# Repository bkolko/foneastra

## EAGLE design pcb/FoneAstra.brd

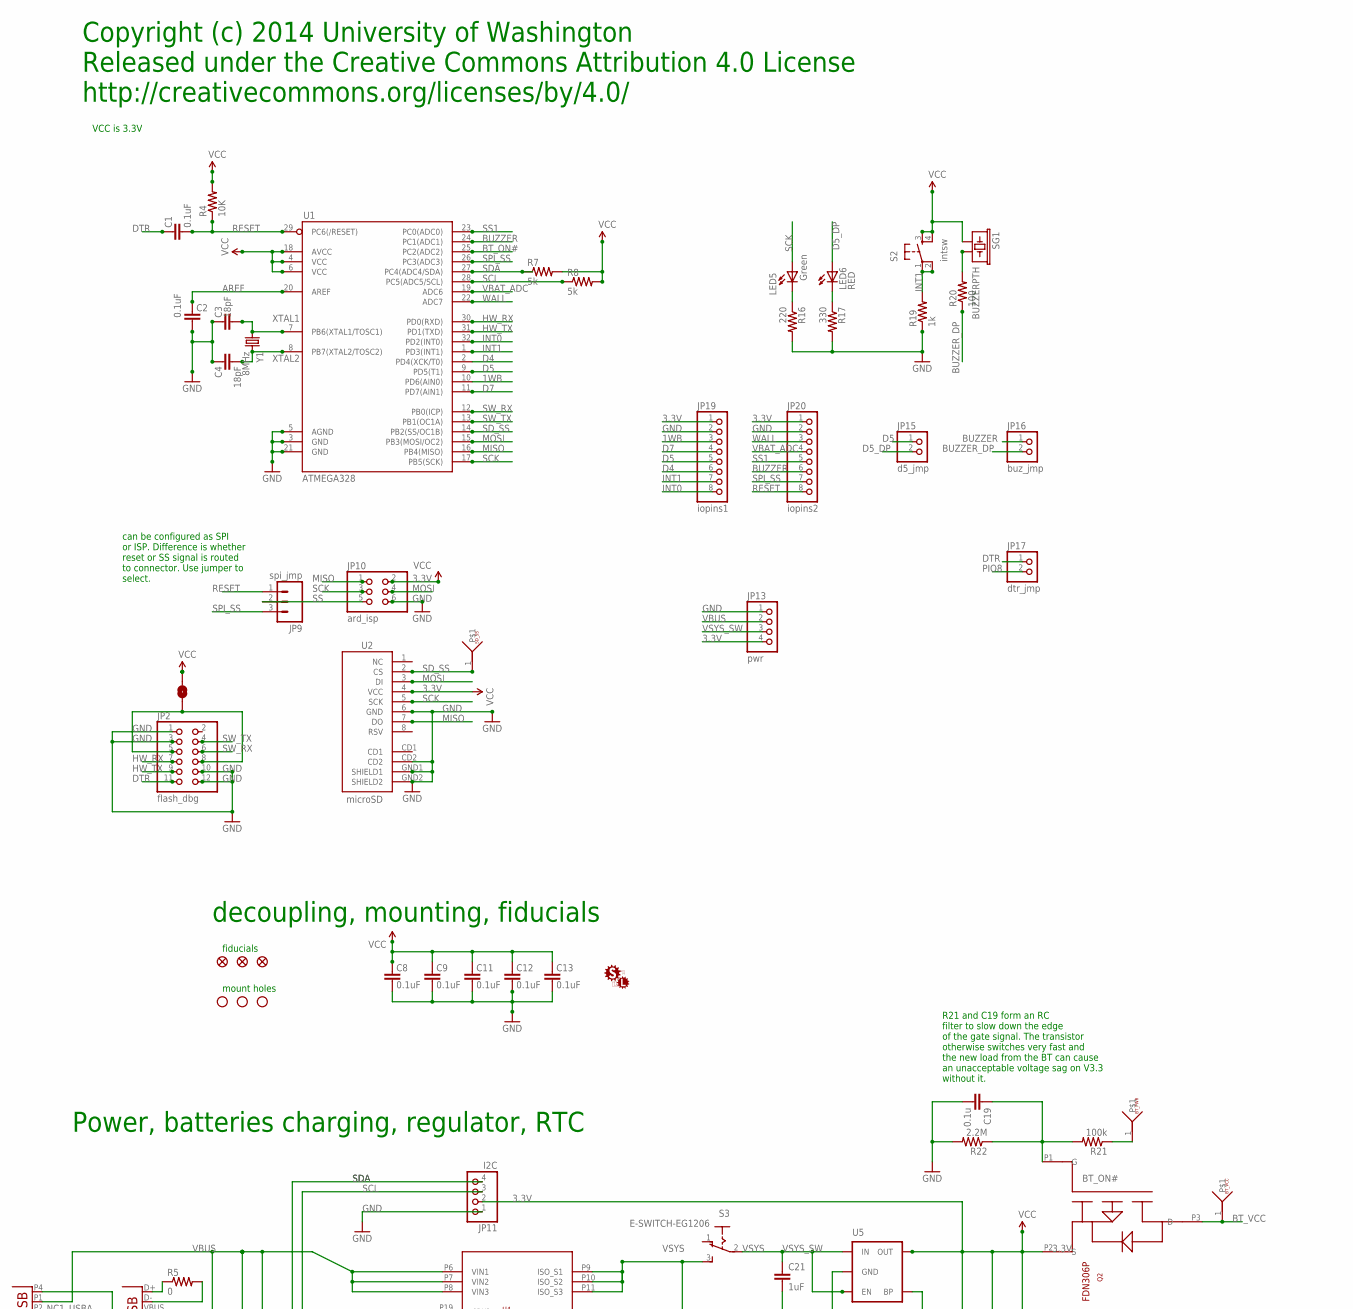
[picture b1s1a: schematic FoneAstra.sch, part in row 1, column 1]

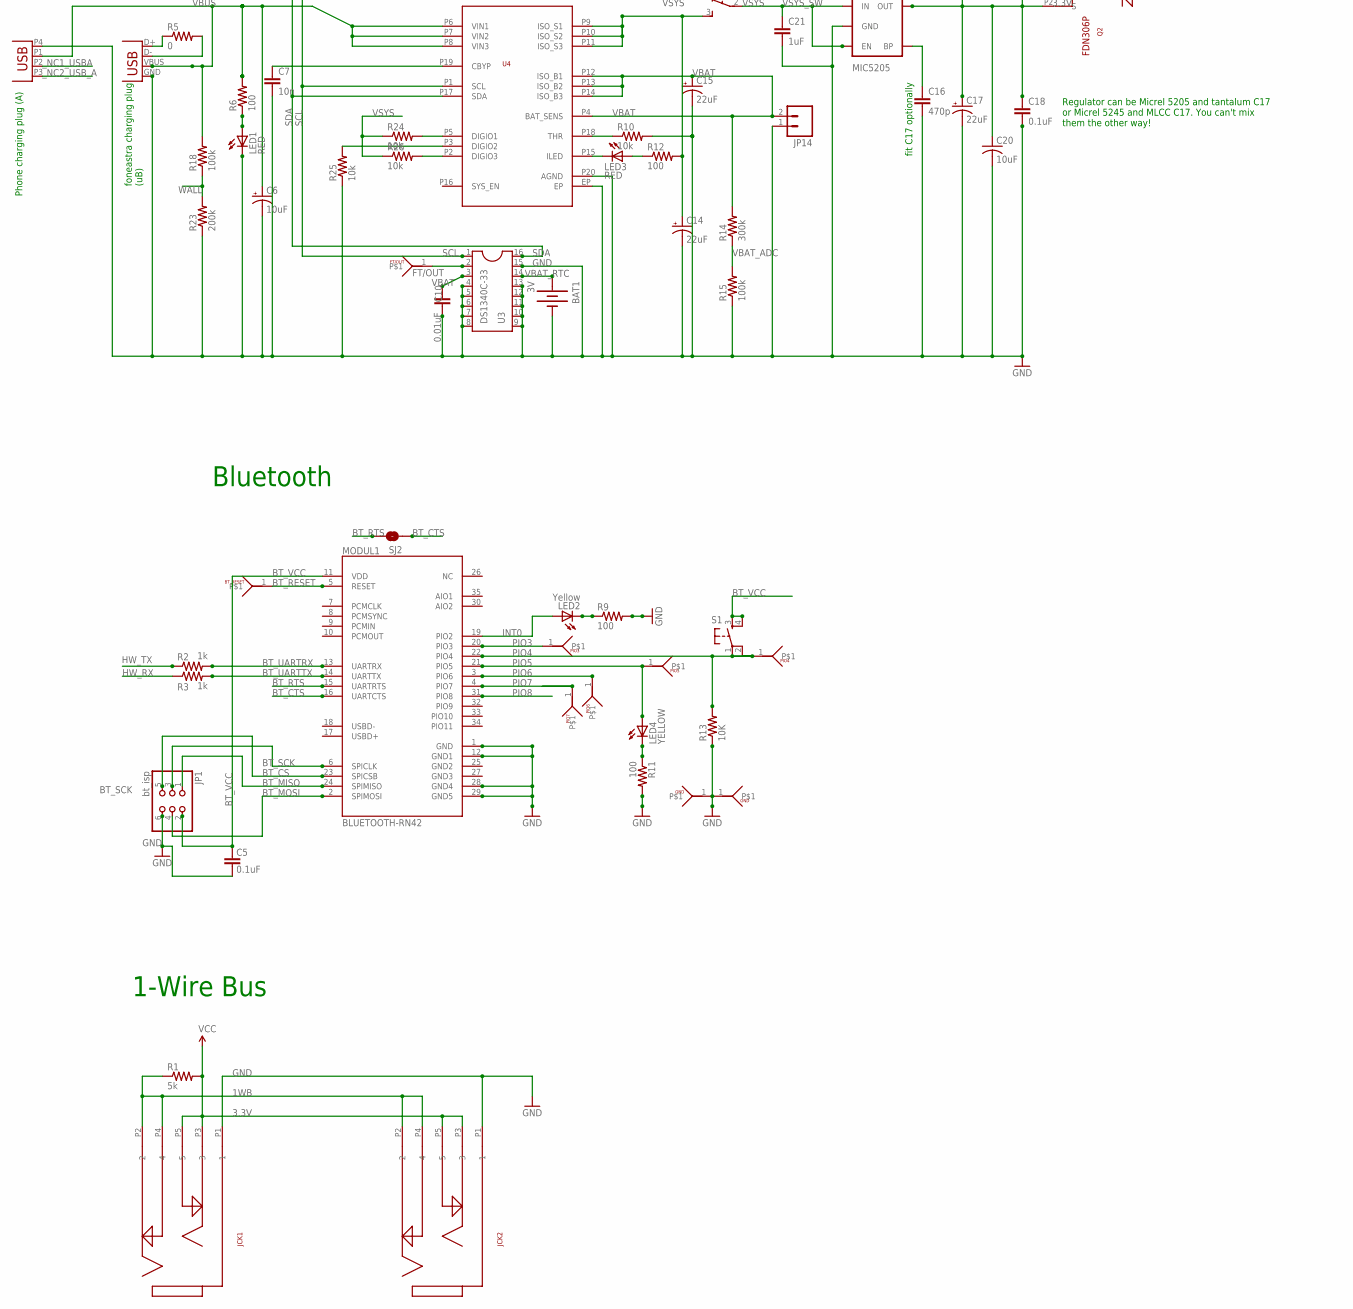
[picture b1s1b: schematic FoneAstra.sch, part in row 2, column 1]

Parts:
BAT1: 3V; BATTCON_12MM_CURVED
C1, C2, C5, C8, C9, C11, C12, C13, C18: 0.1uF; 0402-CAP
C3, C4: 18pF; 0402-CAP
C6: 10uF; EIA3216
C7: 10n; 0402-CAP
C10: 0.01uF; 0402-CAP
C14, C15, C17: 22uF; EIA3216
C16: 470p; 0402-CAP
C19: 0.1u; 0402-CAP
C20: 10uF; C0805
C21: 1uF; 0402-CAP
JCK1, JCK2: 35RASMT4BHNTRX
JP1: bt_isp; 2X03
JP2: flash_dbg; 2X06
JP3, JP5, JP7: SPARKFUN_FIDUCIAL1.5X3; SPARKFUN_FIDUCIAL-1.5X3
JP4, JP6, JP8: STAND-OFFTIGHT; STAND-OFF-TIGHT
JP9: spi_jmp; 1X03
JP10: ard_isp; 2X03
JP11: I2C; 1X04
JP13: pwr; 1X04
JP14: SPARKFUN_M02JST-PTH-2; SPARKFUN_JST-2-PTH
JP15: d5_jmp; 1X02
JP16: buz_jmp; 1X02
JP17: dtr_jmp; 1X02
JP19: iopins1; 1X08
JP20: iopins2; 1X08
LED1, LED3, LED6: RED; LXH4
LED2: Yellow; LXH4
LED4: YELLOW; LED-0603
LED5: Green; LED-0603
MODUL1: BLUETOOTH-RN42; SPARKFUN_RN41
Q2: FDN306P; MYSOT23
R1, R7, R8: 5k; 0402-RES
R2, R3, R19: 1k; 0402-RES
R4, R13: 10K; 0402-RES
R5: 0; 0402-RES
R6, R9, R11, R12, R20: 100; 0402-RES
R10, R24, R25, R26: 10k; 0402-RES
R14: 300k; 0402-RES
R15, R18, R21: 100k; 0402-RES
R16: 220; 0402-RES
R17: 330; 0402-RES
R22: 2.2M; 0402-RES
R23: 200k; 0402-RES
S1: Reset; TACTILE_SWITCH_SMD
S2: intsw; SPARKFUN_TACTILE_SWITCH_SMD
S3: E-SWITCH-EG1206; EG1206
SG1: BUZZERPTH; BUZZER-12MM
SJ1, SJ2: SOLDERJUMPERNC2; SJ_2S-NOTRACE
TP1: BT_RESET; TESTPOINT
TP2: FT/OUT; TESTPOINT
TP3: SD_SS; TESTPOINT
TP4: PIO3; TESTPOINT
TP5: PIO7; TESTPOINT
TP6: PIO6; TESTPOINT
TP7: PIO5; TESTPOINT
TP8, TP9: GND; TESTPOINT
TP10: PIO4; TESTPOINT
TP11: BT_PWR; TESTPOINT
TP12: BT_VCC; TESTPOINT
U1: ATMEGA328; TQFP32-08
U2: microSD; SPARKFUN_MICRO-SD-SOCKET-PP
U3: DS1340C-33; SO16L
U4: ADP5062; LFCSP_WQ20
U5: MIC5205; SOT23-5
U$2: SHIFT_LOGO
X1: MOLEX48204_USB_A_VERT
X2: Micro USB; USB-MICROB
Y1: 8MHz; HC49/S

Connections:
1WB: JCK1.P2 (2), JCK1.P4 (4), JCK2.P2 (2), JCK2.P4 (4), JP19.3, R1.1, U1.10 (PD6(AIN0))
3.3V: C8.2, C9.2, C11.2, C12.2, C13.2, C17.A (+), C18.1, C20.1, JCK1.P3 (3), JCK1.P5 (5), JCK2.P3 (3), JCK2.P5 (5), JP10.2, JP11.2, JP13.4, JP19.1, JP20.1, Q2.P2 (S), R1.2, R4.2, R7.2, R8.2, S2.3, S2.4, SG1.+ (1), SJ1.1, U1.4 (VCC), U1.6 (VCC), U1.18 (AVCC), U2.4 (VCC), U5.5 (OUT)
AREF: C2.2, U1.20 (AREF)
BT_CS: JP1.5, MODUL1.23 (SPICSB)
BT_CTS: MODUL1.16 (UARTCTS), SJ2.1
BT_MISO: JP1.1, MODUL1.24 (SPIMISO)
BT_MOSI: JP1.4, MODUL1.2 (SPIMOSI)
BT_ON#: R21.1, TP11.1, U1.25 (PC2(ADC2))
BT_ON_G: C19.1, Q2.P1 (G), R21.2, R22.1
BT_RESET: MODUL1.5 (RESET), TP1.1
BT_RTS: MODUL1.15 (UARTRTS), SJ2.2
BT_SCK: JP1.3, MODUL1.6 (SPICLK)
BT_UARTRX: MODUL1.13 (UARTRX), R2.2
BT_UARTTX: MODUL1.14 (UARTTX), R3.2
BT_VCC: C5.2, JP1.2, MODUL1.11 (VDD), Q2.P3 (D), S1.3, S1.4, TP12.1
BUZZER: JP16.1, JP20.6, U1.24 (PC1(ADC1))
BUZZER_DP: JP16.2, R20.1
CHG_L_2: LED3.K (C), U4.P15 (ILED)
CHG_THR: R10.1, U4.P18 (THR)
CH_L1: LED3.A, R12.1
D1: LED4.C, R11.1
D4: JP19.6, U1.2 (PD4(XCK/T0))
D5: JP15.1, JP19.5, U1.9 (PD5(T1))
D5_DP: JP15.2, LED6.A
D7: JP19.4, U1.11 (PD7(AIN1))
DTR: C1.2, JP2.11, JP17.1
FT/OUT: TP2.1, U3.2
GND: BAT1.GND (-), C2.1, C3.2, C4.2, C5.1, C6.C (-), C7.2, C8.1, C9.1, C10.1, C11.1, C12.1, C13.1, C14.C (-), C15.C (-), C16.2, C17.C (-), C18.2, C19.2, C20.2, C21.2, JCK1.P1 (1), JCK2.P1 (1), JP1.6, JP2.1, JP2.3, JP2.10, JP2.12, JP10.6, JP11.1, JP13.1, JP14.1, JP19.2, JP20.2, LED1.K (C), MODUL1.1 (GND), MODUL1.12 (GND1), MODUL1.28 (GND4), MODUL1.29 (GND5), R9.2, R10.2, R11.2, R13.1, R15.1, R16.2, R17.2, R19.1, R22.2, R23.1, R25.1, TP8.1, TP9.1, U1.3 (GND), U1.5 (AGND), U1.21 (GND), U2.6 (GND), U2.CD2, U2.GND1 (SHIELD1), U2.GND2 (SHIELD2), U3.4, U3.5, U3.6, U3.7, U3.8, U3.9, U3.10, U3.11, U3.12, U3.13, U3.15, U4.EP, U4.P20 (AGND), U5.2 (GND), X1.P4 (GND), X2.GND
HW_RX: JP2.7, R3.1, U1.30 (PD0(RXD))
HW_TX: JP2.9, R2.1, U1.31 (PD1(TXD))
INT0: JP19.8, LED2.A, MODUL1.19 (PIO2), U1.32 (PD2(INT0))
INT1: JP19.7, R19.2, S2.1, S2.2, U1.1 (PD3(INT1))
MISO: JP10.1, U1.16 (PB4(MISO)), U2.7 (DO)
MOSI: JP10.4, U1.15 (PB3(MOSI/OC2)), U2.3 (DI)
unnamed: R20.2, SG1.- (2)
unnamed: JP2.5, JP2.8, SJ1.2
unnamed: C7.1, U4.P19 (CBYP)
unnamed: R24.2, U4.P5 (DIGIO1)
unnamed: LED6.K (C), R17.1
unnamed: R26.2, U4.P2 (DIGIO3)
unnamed: LED5.C, R16.1
unnamed: LED2.K (C), R9.1
unnamed: LED1.A, R6.1
unnamed: C16.1, U5.4 (BP)
unnamed: R25.2, U4.P3 (DIGIO2)
unnamed: R5.2, X2.D-
unnamed: R5.1, X2.D+
PIO3: MODUL1.20 (PIO3), TP4.1
PIO4: MODUL1.22 (PIO4), R13.2, S1.1, S1.2, TP10.1
PIO5: LED4.A, MODUL1.21 (PIO5), TP7.1
PIO6: MODUL1.3 (PIO6), TP6.1
PIO7: MODUL1.4 (PIO7), TP5.1
PIO8: JP17.2, MODUL1.31 (PIO8)
RESET: C1.1, JP9.1, JP20.8, R4.1, U1.29 (PC6(/RESET))
SCK: JP10.3, LED5.A, U1.17 (PB5(SCK)), U2.5 (SCK)
SCL: JP11.3, R8.1, U1.28 (PC5(ADC5/SCL)), U3.1, U4.P1 (SCL)
SDA: JP11.4, R7.1, U1.27 (PC4(ADC4/SDA)), U3.16, U4.P17 (SDA)
SD_SS: TP3.1, U1.14 (PB2(SS/OC1B)), U2.2 (CS)
SPI_SS: JP9.3, JP20.7, U1.26 (PC3(ADC3))
SS: JP9.2, JP10.5
SS1: JP20.5, U1.23 (PC0(ADC0))
SW_RX: JP2.6, U1.12 (PB0(ICP))
SW_TX: JP2.4, U1.13 (PB1(OC1A))
VBAT: C10.2, C15.A (+), JP14.2, R14.2, U3.3, U4.P4 (BAT_SENS), U4.P12 (ISO_B1), U4.P13 (ISO_B2), U4.P14 (ISO_B3)
VBAT_ADC: JP20.4, R14.1, R15.2, U1.19 (ADC6)
VBAT_RTC: BAT1.PWR@1 (+), U3.14
VBUS: C6.A (+), JP13.2, R6.2, R18.2, U4.P6 (VIN1), U4.P7 (VIN2), U4.P8 (VIN3), X1.P1 (VBUS), X2.VBUS
VSYS: C14.A (+), R12.2, R24.1, R26.1, S3.3 (S), U4.P9 (ISO_S1), U4.P10 (ISO_S2), U4.P11 (ISO_S3)
VSYS_SW: C21.1, JP13.3, S3.2, U5.1 (IN), U5.3 (EN)
WALL: JP20.3, R18.1, R23.2, U1.22 (ADC7)
XTAL1: C3.1, U1.7 (PB6(XTAL1/TOSC1)), Y1.1
XTAL2: C4.1, U1.8 (PB7(XTAL2/TOSC2)), Y1.2
_NC1_USBA: X1.P2 (D-)
_NC2_USB_A: X1.P3 (D+)

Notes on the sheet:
VCC is 3.3V
Copyright (c) 2014 University of Washington Released under the Creative Commons Attribution 4.0 License http://creativecommons.org/licenses/by/4.0/
Phone charging plug (A)
fiducials
mount holes
Power, batteries charging, regulator, RTC
1-Wire Bus
Bluetooth
decoupling, mounting, fiducials
fit C17 optionally
foneastra charging plug (uB)
can be configured as SPI or ISP. Difference is whether reset or SS signal is routed to connector. Use jumper to select.
R21 and C19 form an RC filter to slow down the edge of the gate signal. The transistor otherwise switches very fast and the new load from the BT can cause an unacceptable voltage sag on V3.3 without it.
Regulator can be Micrel 5205 and tantalum C17 or Micrel 5245 and MLCC C17. You can't mix them the other way!

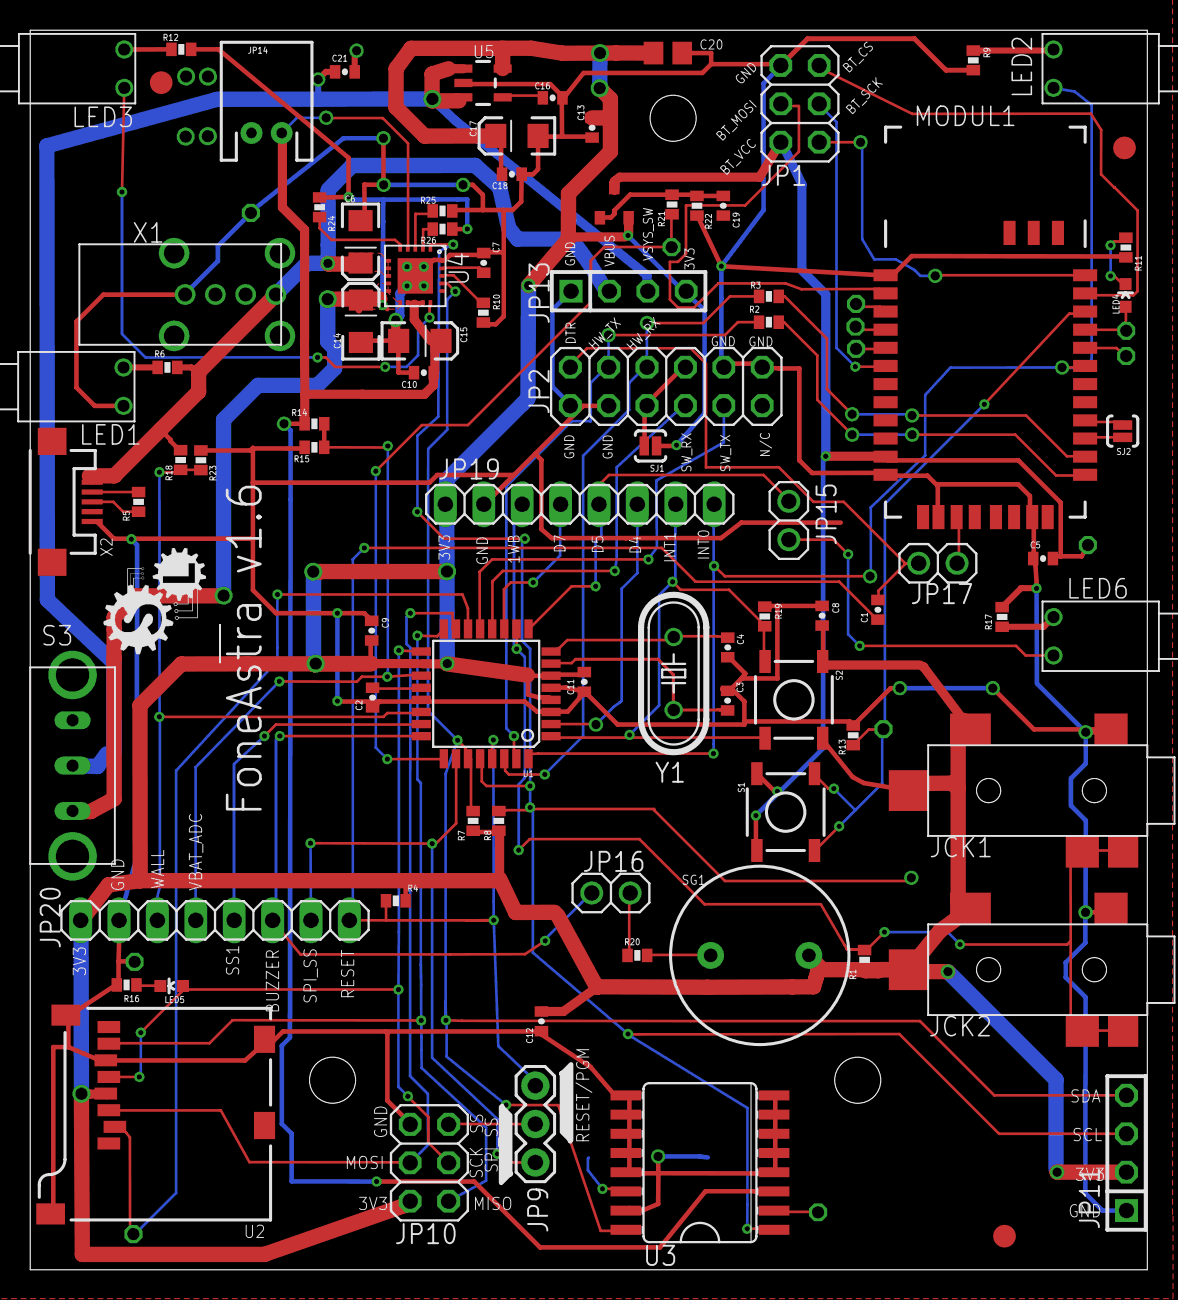
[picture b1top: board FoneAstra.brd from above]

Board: 2 copper layers, 73.9 x 82.0 mm, 103 parts (1 on the bottom side), 72 nets.

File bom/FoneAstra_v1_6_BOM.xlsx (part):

Part | Value | Device | Package | Description | SparkFun | Manufacturer | Manufacturer # | Mouser | Digikey | INCLUDE | Qty | Note
BAT1 | 3V | BATTERY | BATTCON_12MM_CURVED | Battery Holders | http://www.sparkfun.com/products/10592 | MPD (Memory Protection Devices) | BK-885-TR | 534-3000 | BK-885TR-ND |  | 0
C1 | 0.1uF | CAP0402-CAP | 0402-CAP | Capacitor |  | TDK Corporation | C1005X7R1H104K050BB | 810-C1005X7R1H104K | 445-13671-1-ND | x | 1
C10 | 10nF | CAP0402-CAP | 0402-CAP | Capacitor |  | Vishay BC Components | VJ0402Y103KXJCW1BC | 77-VJ0402Y103KXJCBC | BC1217TR-ND | x | 1
C11 | 0.1uF | CAP0402-CAP | 0402-CAP | Capacitor |  | TDK Corporation | C1005X7R1H104K050BB | 810-C1005X7R1H104K | 445-13671-1-ND | x | 1
C12 | 0.1uF | CAP0402-CAP | 0402-CAP | Capacitor |  | TDK Corporation | C1005X7R1H104K050BB | 810-C1005X7R1H104K | 445-13671-1-ND | x | 1
C13 | 0.1uF | CAP0402-CAP | 0402-CAP | Capacitor |  | TDK Corporation | C1005X7R1H104K050BB | 810-C1005X7R1H104K | 445-13671-1-ND | x | 1
C14 | 22uF | CAP_POL1206 | EIA3216 | Capacitor Polarized |  | TDK Corporation | C3216X5R0J226M | 810-C3216X5R0J226M | 445-7717-1-ND | x | 1 | note the part is not really polarized, just the EAGLE footprint
C15 | 22uF | CAP_POL1206 | EIA3216 | Capacitor Polarized |  | TDK Corporation | C3216X5R0J226M | 810-C3216X5R0J226M | 445-7717-1-ND | x | 1 | note the part is not really polarized, just the EAGLE footprint
C16 | 470p | CAP0402-CAP | 0402-CAP | Capacitor |  | Samsung Electro-Mechanics America, Inc | CL05B471KB5NNNC | 581-04025C471K | 1276-1566-1-ND | x | 1
C17 | 22uF | CAP_POL1206 | EIA3216 | Capacitor Polarized |  | TDK Corporation | C3216X5R0J226M | 810-C3216X5R0J226M | 445-7717-1-ND | x | 1
C18 | 0.1uF | CAP0402-CAP | 0402-CAP | Capacitor |  | TDK Corporation | C1005X7R1H104K050BB | 810-C1005X7R1H104K | 445-13671-1-ND | x | 1
C19 | 0.1uF | CAP0402-CAP | 0402-CAP | Capacitor |  | TDK Corporation | C1005X7R1H104K050BB | 810-C1005X7R1H104K | 445-13671-1-ND | x | 1 | model tbd
C20 | 10uf | CAP0805-CAP | 0805-CAP | Capacitor |  | TDK Corporation | C2012X7R0J106K125AB |  | 445-7593-1-ND | x | 1 | extra cap on 3V3. With BT soft start, may not be necessary. Chose 0805 because 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
C21 | 1uF | CAP0402-CAP | 0402-CAP | Capacitor |  | TDK Corporation | C1005X5R1A105K050BB |  | 445-4114-1-ND | x
C2 | 0.1uF | CAP0402-CAP | 0402-CAP | Capacitor |  | TDK Corporation | C1005X7R1H104K050BB | 810-C1005X7R1H104K | 445-13671-1-ND | x | 1
C3 | 18pF | CAP0402-CAP | 0402-CAP | Capacitor |  | TDK Corporation | C1005C0G1H180J050BA | 810-C1005C0G1H180J | 445-1238-1-ND | x | 1
C4 | 18pF | CAP0402-CAP | 0402-CAP | Capacitor |  | TDK Corporation | C1005C0G1H180J050BA | 810-C1005C0G1H180J | 445-1238-1-ND | x | 1
C5 | 0.1uF | CAP0402-CAP | 0402-CAP | Capacitor |  | TDK Corporation | C1005X7R1H104K050BB | 810-C1005X7R1H104K | 445-13671-1-ND | x | 1
C6 | 10uF | CAP_POL1206 | EIA3216 | Capacitor Polarized |  | TDK Corporation | C3216X5R1C106M160AA | 810-C3216X5R1C106M | 445-1426-1-ND | x | 1 | note the part is not really polarized, just the EAGLE footprint
C7 | 10n | CAP0402-CAP | 0402-CAP | Capacitor |  | Vishay BC Components | VJ0402Y103KXJCW1BC | 77-VJ0402Y103KXJCBC | BC1217TR-ND | x | 1
C8 | 0.1uF | CAP0402-CAP | 0402-CAP | Capacitor |  | TDK Corporation | C1005X7R1H104K050BB | 810-C1005X7R1H104K | 445-13671-1-ND | x | 1
C9 | 0.1uF | CAP0402-CAP | 0402-CAP | Capacitor |  | TDK Corporation | C1005X7R1H104K050BB | 810-C1005X7R1H104K | 445-13671-1-ND | x | 1
JCK1 | 35RASMT4BHNTRX | 35RASMT4BHNTRX | 35RASMT4BHNTRX |  |  | Switchcraft Inc. | SC1488-1-ND | 502-35RASMT4BHNTRX | SC1488-1-ND |  | 0
JCK2 | 35RASMT4BHNTRX | 35RASMT4BHNTRX | 35RASMT4BHNTRX |  |  | Switchcraft Inc. | SC1488-1-ND | 502-35RASMT4BHNTRX | SC1488-1-ND | x | 1 | not fitting this part now
JCK3 | 35RASMT4BHNTRX | 35RASMT4BHNTRX | 35RASMT4BHNTRX |  |  | Switchcraft Inc. | SC1488-1-ND | 502-35RASMT4BHNTRX | SC1488-1-ND |  | 0 | not fitting this part not
JP1 | bt_isp | PINHD-2X3 | 2X03 | PIN HEADER | https://www.sparkfun.com/products/12807 | FCI | 67996-206HLF |  | 609-3210-ND | x | 1 | do we meed to install this header in production boards?
JP10 | ard_isp | PINHD-2X3 | 2X03 | PIN HEADER | https://www.sparkfun.com/products/12807 | FCI | 67996-206HLF |  | 609-3210-ND | x | 1 | Can be made from strip(s) of 0.1 breakaway
JP11 | I2C | PINHD-1X4 | 1X04 | PIN HEADER |  | 3M | 961104-6404-AR | 517-9611046404AR |  |  | 0 | Can be made from strip(s) of 0.1 breakaway
JP19 | iopins1 | PINHD-1X8 | 1X08 | PIN HEADER |  | Harwin Inc | M20-9990846 | 649-68418-413HLF | 952-2271-ND |  | 0 | Can be made from strip(s) of 0.1 breakaway
JP20 | iopins2 | PINHD-1X8 | 1X08 | PIN HEADER |  | Harwin Inc | M20-9990846 | 855-M20-9990846 | 952-2271-ND |  | 0 | Can be made from strip(s) of 0.1 breakaway
JP13 | pwr | PINHD-1X4 | 1X04 | PIN HEADER |  | 3M | 961104-6404-AR | 517-9611046404AR |  |  | 0 | Can be made from strip(s) of 0.1 breakaway
JP14 | battconn | M02JST-PTH | JST-2-PTH | 2 pin JST header | https://www.sparkfun.com/products/9749 | JST Sales America Inc | S2B-PH-K-S(LF)(SN) |  | 455-1719-ND | x | 1 | need to doublecheck digikey is same as SF
JP15 | d5_jmp | PINHD-1X2 | 1X02 | PIN HEADER |  | 3M | 961102-6404-AR | 517-9611026404AR |  |  | 0 | Can be made from strip(s) of 0.1 breakaway
JP16 | buz_jmp | PINHD-1X2 | 1X02 | PIN HEADER |  | 3M | 961102-6404-AR | 517-9611026404AR |  |  | 0 | Can be made from strip(s) of 0.1 breakaway
JP17 | dtr_jmp | PINHD-1X2 | 1X02 | PIN HEADER |  | 3M | 961102-6404-AR | 517-9611026404AR |  |  | 0 | Can be made from strip(s) of 0.1 breakaway
JP2 | flash_dbg | PINHD-2X6 | 2X06 | PIN HEADER |  |  |  |  |  |  | 0 | Can be made from strip(s) of 0.1 breakaway
JP3 | SPARKFUN_FIDUCIAL1.5X3 | SPARKFUN_FIDUCIAL1.5X3 | SPARKFUN_FIDUCIAL-1.5X3 | Fiducial Alignment Points |  |  |  |  |  |  | 0 | not a part
JP4 | STAND-OFFTIGHT | STAND-OFFTIGHT | STAND-OFF-TIGHT | #4 Stand Off |  |  |  |  |  |  | 0 | not a part
JP5 | SPARKFUN_FIDUCIAL1.5X3 | SPARKFUN_FIDUCIAL1.5X3 | SPARKFUN_FIDUCIAL-1.5X3 | Fiducial Alignment Points |  |  |  |  |  |  | 0 | not a part |  |  | may want to consider enlarging this to 2x8 to find more parts
JP6 | STAND-OFFTIGHT | STAND-OFFTIGHT | STAND-OFF-TIGHT | #4 Stand Off |  |  |  |  |  |  | 0 | not a part
JP7 | SPARKFUN_FIDUCIAL1.5X3 | SPARKFUN_FIDUCIAL1.5X3 | SPARKFUN_FIDUCIAL-1.5X3 | Fiducial Alignment Points |  |  |  |  |  |  | 0 | not a part
JP8 | STAND-OFFTIGHT | STAND-OFFTIGHT | STAND-OFF-TIGHT | #4 Stand Off |  |  |  |  |  |  | 0 | not a part
JP9 | spi_jmp | M03PTH | 1X03 | Header 3 |  | 3M | 961103-6804-AR | 517-9611036804AR | 961103-6804-AR-ND | x | 1 | Can be made from strip(s) of 0.1 breakaway
LED1 | RED | LED | LXH4 | LEDs |  | Lumex Opto/Components Inc | SSF-LXH4RAID |  | 67-1303-ND | x | 1
LED2 | YELLOW | LED | LXH4 | LEDs |  | Lumex Opto/Components Inc | SSF-LXH4RAYD |  | 67-1305-ND | x | 1 | Note: LXH series has no blue. This is green. There is only red, green, yellow i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
LED3 | RED | LED | LXH4 | LEDs |  | Lumex Opto/Components Inc | SSF-LXH4RAID |  | 67-1303-ND | x | 1
LED4 | YELLOW | LED0603 | LED-0603 | LEDs |  | Vishay Semiconductor Opto Division | TLMY1100-GS08 | 720-LYQ976-P1S2-36 | 751-1186-1-ND | x | 1
LED5 | Green | LED0603 | LED-0603 | LEDs |  | Stanley Electric Co | PG1111C-TR | 720-LGQ971-KN-1 | 404-1004-1-ND | x | 1
LED6 | RED | LED | LXH4 | LEDs |  | Lumex Opto/Components Inc | SSF-LXH4RAID |  | 67-1303-ND | x | 1 | Note: LXH series has no blue. This is green. There is only red, green, yellow i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
Y1 | 8MHz | CRYSTALHC49S | HC49/S | CRYSTAL |  | CTS-Frequency Controls | ATS080B | 695-HC49US-8-U | CTX900-ND | x | 1
Q2 | FDN306P | FDN306P | MYSOT23 |  |  | Fairchild Semiconductor | FDN306P | 512-FDN306P | FDN306PCT-ND | x | 1
R1 | 5k | RESISTOR0402-RES | 0402-RES | Resistor |  | Panasonic Electronic Components | ERJ-2GEJ512X |  | P5.1KJCT-ND | x | 1 | note: none of these resistor tolerances are very important, go with cheapest
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
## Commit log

2015-03-05 Adding the Apache License
2015-03-05 removed Apache license, in favor of Creative Commons
2015-03-05 Adding the PCB, test sketch, BOM, and programming instructions
2015-06-15 Added CAD files
2015-11-03 added hardware BOM
2016-03-08 Uploaded Gerbers
    Added gerber files for PCB

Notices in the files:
parts and their libraries:
SparkFun-Electromechanical: Licensing: CC v3.0 Share-Alike You are welcome to use this library for commercial purposes.
